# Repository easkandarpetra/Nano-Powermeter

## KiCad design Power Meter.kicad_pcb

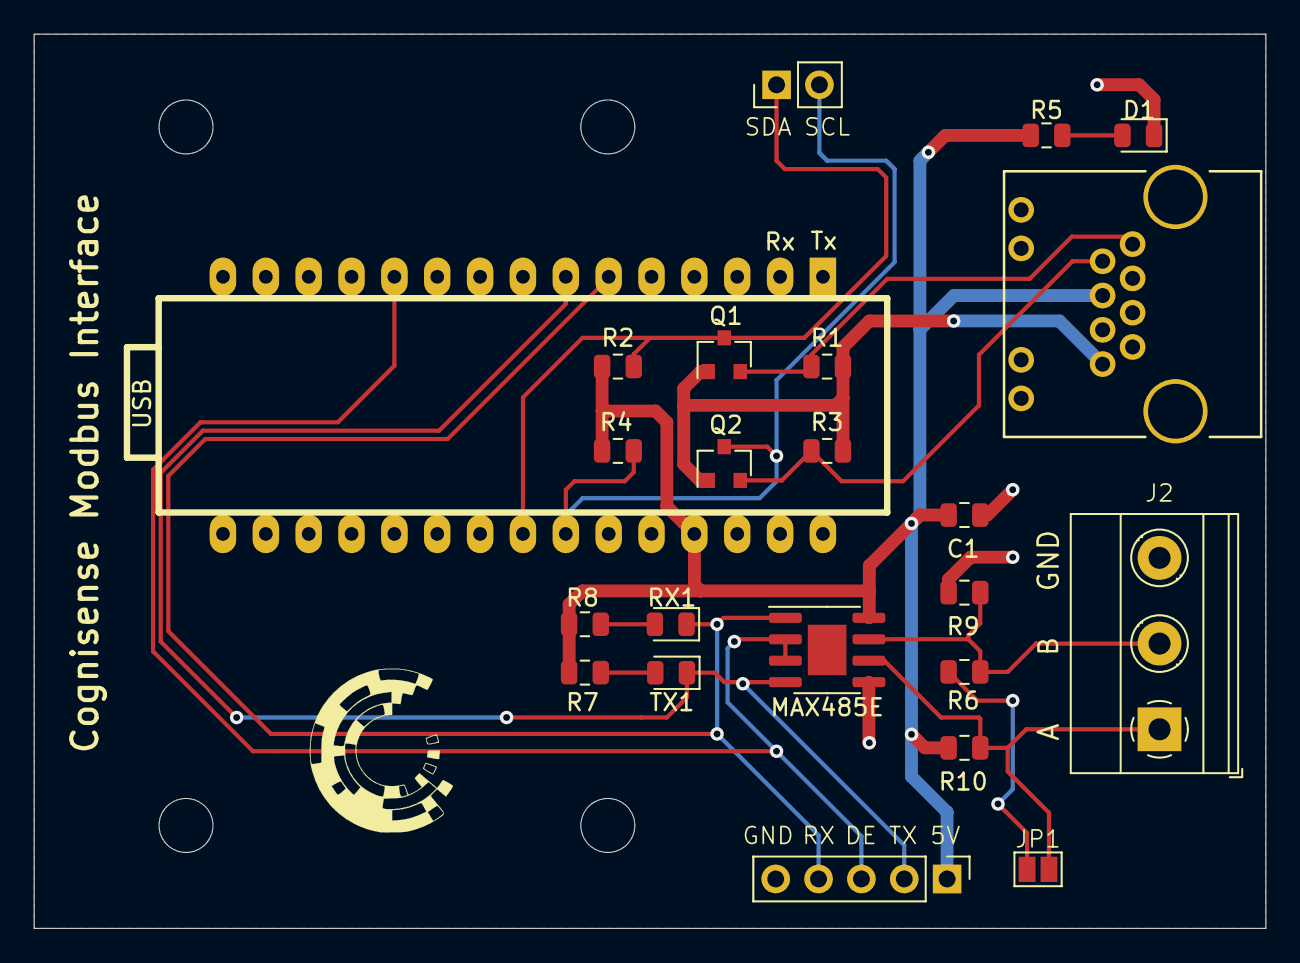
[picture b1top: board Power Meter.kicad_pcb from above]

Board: 2 copper layers, 73.0 x 53.0 mm, 27 parts (0 on the bottom side), 16 nets.

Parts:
A1: Arduino_Nano; arduino_nano2
C1: 0.1uF; C_0805_2012Metric
D1: LED; LED_0805_2012Metric
J1: RJ45_LED; CONNECTOR_RJ45_RA_TH_LEDS
J2: Screw_Terminal_01x03; TerminalBlock_Phoenix_MKDS-1,5-3-5.08_1x03_P5.08mm_Horizont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
J3: Conn_01x05; PinHeader_1x05_P2.54mm_Vertical
J4: Conn_01x02; PinHeader_1x02_P2.54mm_Vertical
JP1: SolderJumper_2_Open; SolderJumper-2_P1.3mm_Open_Pad1.0x1.5mm
M3, M3#2, M3#3, M3#4: MountingHole_3.2mm_M3
Q1, Q2: BSS138; SOT-23
R1, R2, R3, R4: 10k; R_0805_2012Metric
R5, R7, R8: 1k; R_0805_2012Metric
R6: 120; R_0805_2012Metric
R9, R10: 10K; R_0805_2012Metric
RX1: LED; LED_0805_2012Metric
TX1: LED; LED_0805_2012Metric
U1: MAX485E; SOIC-8-1EP_3.9x4.9mm_P1.27mm_EP2.29x3mm

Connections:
+3V3: J1.8, Q1.1, Q2.1, R1.1, R3.1
+5V: A1.27, C1.1, J1.4, J3.1, R2.1, R4.1, R5.1, R7.1, R8.1, R10.2, U1.8
D3: A1.6, J3.4, RX1.1, U1.1
D4: A1.7, J3.2, TX1.1, U1.4
D8: A1.11, J3.3, U1.2, U1.3
GND: A1.4, A1.29, C1.2, D1.1, J1.5, J1.7, J2.3, J3.5, R9.1, U1.5
unnamed: D1.2, R5.2
unnamed: J2.1, JP1.2, R10.1, U1.6
unnamed: J2.2, R6.1, R9.2, U1.7
unnamed: JP1.1, R6.2
unnamed: R7.2, TX1.2
unnamed: R8.2, RX1.2
SCL-HV: A1.24, J4.2, Q2.3, R4.2
SCL-LV: J1.2, Q2.2, R3.2
SDA-HV: A1.23, J4.1, Q1.3, R2.2
SDA-LV: J1.1, Q1.2, R1.2

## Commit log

2022-04-13 Update code - change parameters selection
2022-04-13 Add updated circuit files
